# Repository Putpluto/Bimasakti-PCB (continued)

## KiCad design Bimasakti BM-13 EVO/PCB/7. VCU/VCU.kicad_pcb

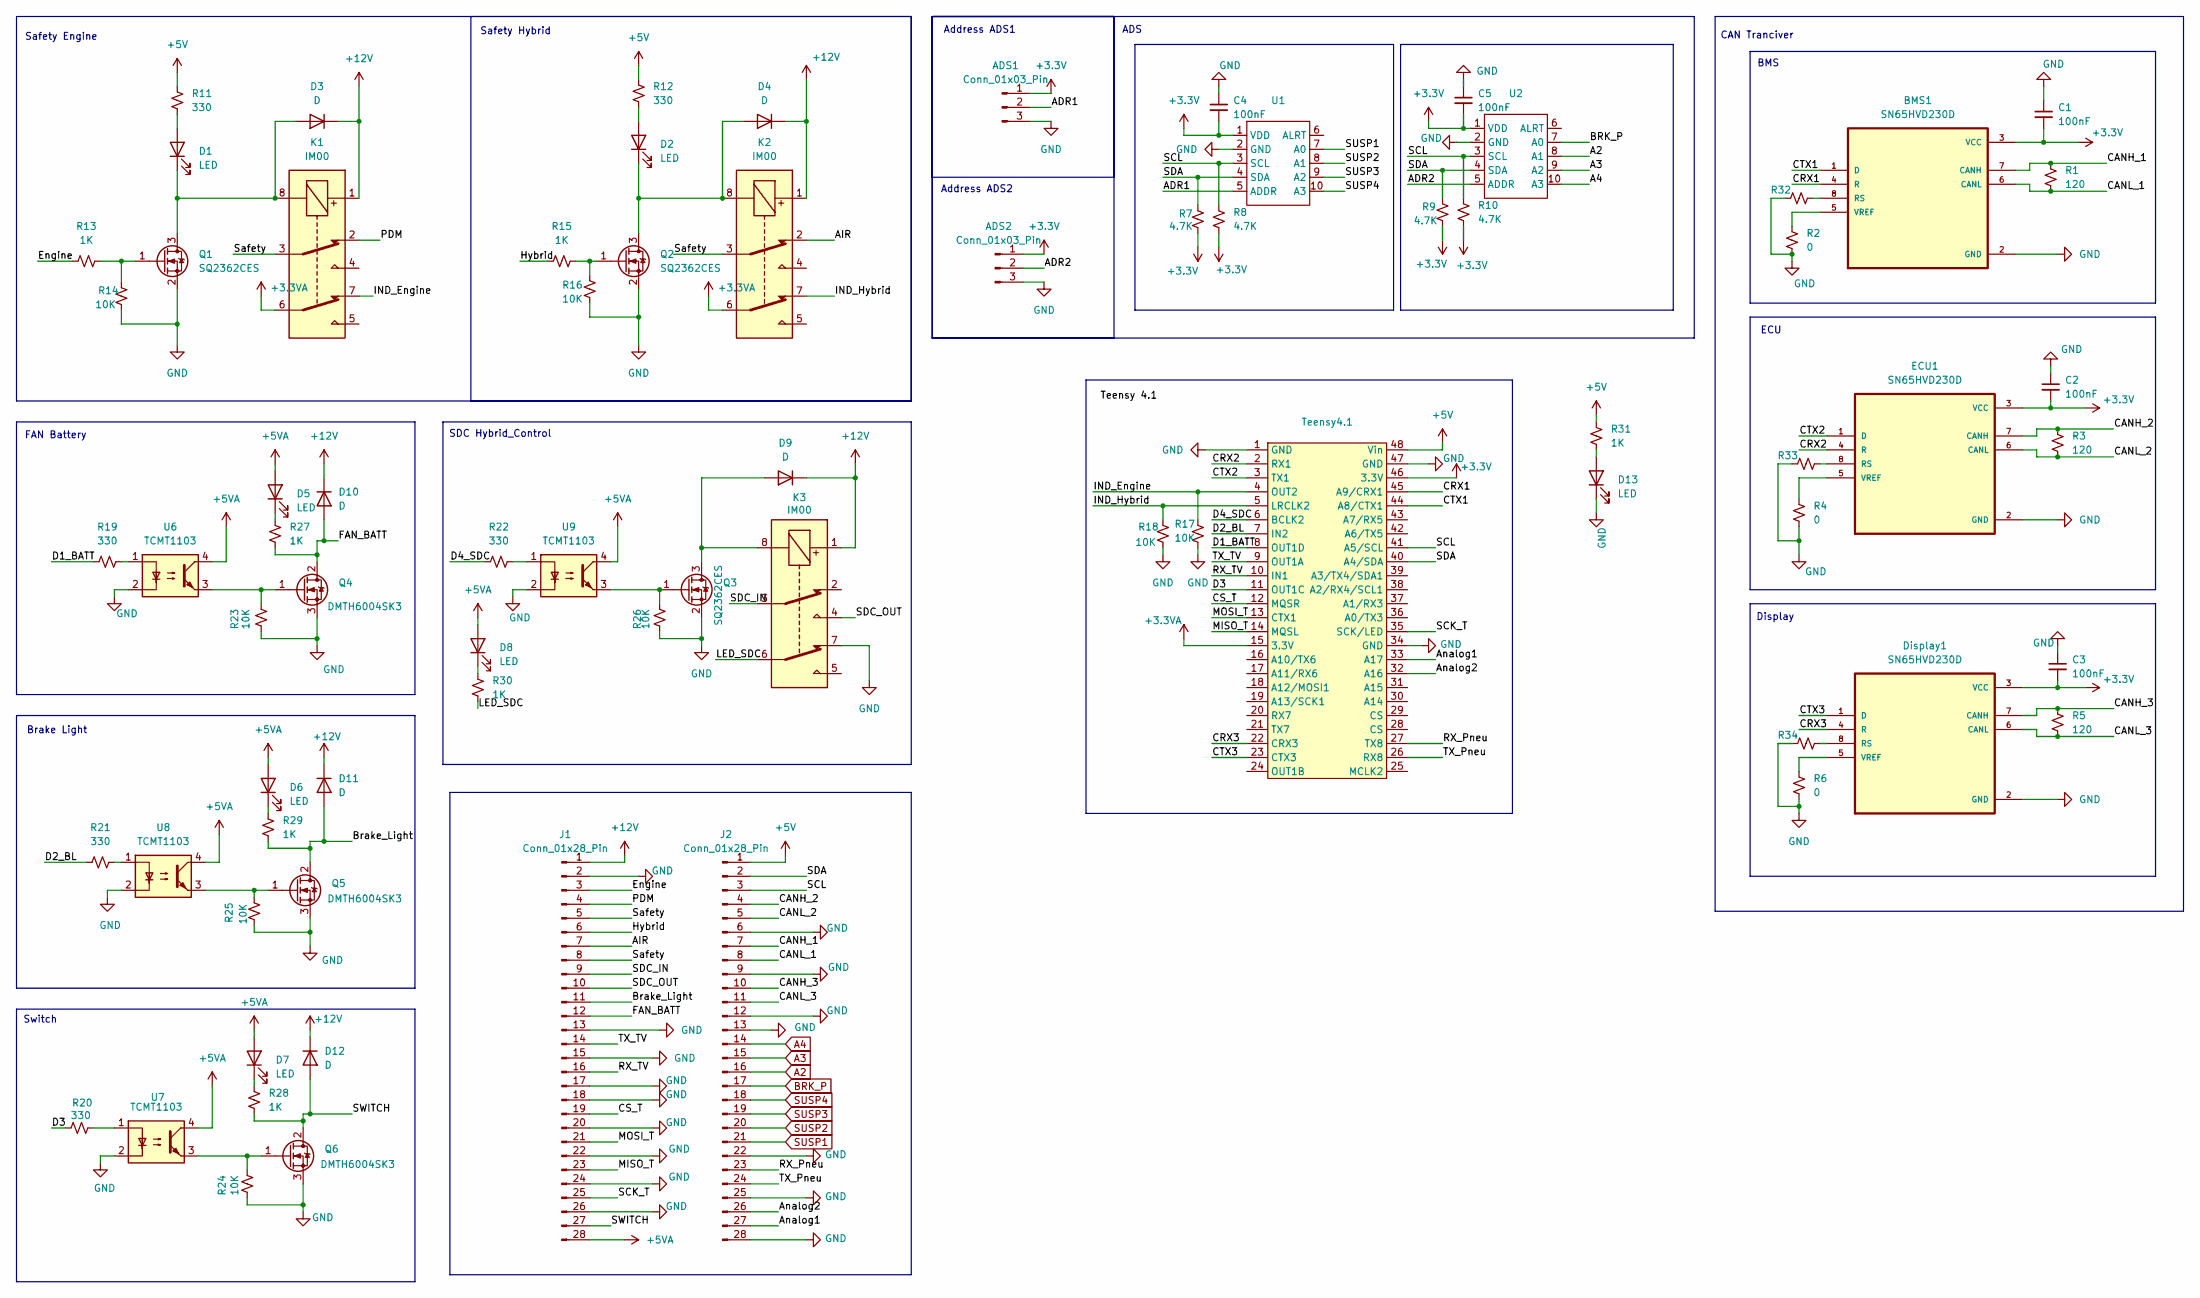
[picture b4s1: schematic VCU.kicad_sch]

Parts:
ADS1, ADS2: Conn_01x03_Pin; PinHeader_1x03_P2.54mm_Vertical
BMS1: SN65HVD230D; SOIC127P599X175-8N
C1, C2, C3, C4, C5: 100nF; C_0603_1608Metric_Pad1.08x0.95mm_HandSolder
D1, D2, D5, D6, D7, D8, D13: LED; LED_0603_1608Metric_Pad1.05x0.95mm_HandSolder
D3, D4, D9, D10, D11, D12: D; D_SOD-123
Display1: SN65HVD230D; SOIC127P599X175-8N
ECU1: SN65HVD230D; SOIC127P599X175-8N
J1, J2: Conn_01x28_Pin; PinHeader_1x28_P2.54mm_Vertical
K1, K2, K3: IM00; RELAY8-TH_NON-LATCH_1-COIL
Q1, Q2, Q3: SQ2362CES; SOT-23
Q4, Q5, Q6: DMTH6004SK3; TO-252-2
R1, R3, R5: 120; R_0603_1608Metric_Pad0.98x0.95mm_HandSolder
R2, R4, R6: 0; R_0603_1608Metric_Pad0.98x0.95mm_HandSolder
R7, R8, R9, R10: 4.7K; R_0603_1608Metric_Pad0.98x0.95mm_HandSolder
R11, R12, R19, R20, R21, R22: 330; R_0603_1608Metric_Pad0.98x0.95mm_HandSolder
R13, R15, R27, R28, R29, R30, R31: 1K; R_0603_1608Metric_Pad0.98x0.95mm_HandSolder
R14, R16, R17, R18, R23, R24, R25, R26: 10K; R_0603_1608Metric_Pad0.98x0.95mm_HandSolder
R32, R33, R34: R_Small_US; R_0603_1608Metric_Pad0.98x0.95mm_HandSolder
Teensy4.1: Teensy41
U1, U2: MSOP10
U6, U7, U8, U9: TCMT1103; SOP-4_4.4x2.6mm_P1.27mm

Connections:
+3.3V: ADS1.1, ADS2.1, BMS1.3 (VCC), C1.2, C2.2, C3.2, C4.2, C5.2, Display1.3 (VCC), ECU1.3 (VCC), R7.2, R8.2, R9.2, R10.2, Teensy4.1.46 (3.3V), U1.1 (VDD), U2.1 (VDD)
+3.3VA: K1.6, K2.6, Teensy4.1.15 (3.3V)
+5V: J2.1, R11.1, R12.1, R31.1, Teensy4.1.48 (Vin)
+5VA: D5.2 (A), D6.2 (A), D7.2 (A), D8.2 (A), J1.28, U6.4, U7.4, U8.4, U9.4
+12V: D3.1 (K), D4.1 (K), D9.1 (K), D10.1 (K), D11.1 (K), D12.1 (K), J1.1, K1.1, K2.1, K3.1
/ADR1: ADS1.2, U1.5 (ADDR)
/ADR2: ADS2.2, U2.5 (ADDR)
/AIR: J1.7, K2.2
/Analog1: J2.27, Teensy4.1.33 (A17)
/Analog2: J2.26, Teensy4.1.32 (A16)
/Brake_Light: D11.2 (A), J1.11, Q5.2 (D), R29.2
/CANH_1: BMS1.7 (CANH), J2.7, R1.1
/CANH_2: ECU1.7 (CANH), J2.4, R3.1
/CANH_3: Display1.7 (CANH), J2.10, R5.1
/CANL_1: BMS1.6 (CANL), J2.8, R1.2
/CANL_2: ECU1.6 (CANL), J2.5, R3.2
/CANL_3: Display1.6 (CANL), J2.11, R5.2
/CRX1: BMS1.4 (R), Teensy4.1.45 (A9/CRX1)
/CRX2: ECU1.4 (R), Teensy4.1.2 (RX1)
/CRX3: Display1.4 (R), Teensy4.1.22 (CRX3)
/CS_T: J1.19, Teensy4.1.12 (MQSR)
/CTX1: BMS1.1 (D), Teensy4.1.44 (A8/CTX1)
/CTX2: ECU1.1 (D), Teensy4.1.3 (TX1)
/CTX3: Display1.1 (D), Teensy4.1.23 (CTX3)
/D1_BATT: R19.1, Teensy4.1.8 (OUT1D)
/D2_BL: R21.1, Teensy4.1.7 (IN2)
/D3: R20.1, Teensy4.1.11 (OUT1C)
/D4_SDC: R22.1, Teensy4.1.6 (BCLK2)
/Engine: J1.3, R13.1
/FAN_BATT: D10.2 (A), J1.12, Q4.2 (D), R27.2
/Hybrid: J1.6, R15.1
/IND_Engine: K1.7, R17.1, Teensy4.1.4 (OUT2)
/IND_Hybrid: K2.7, R18.1, Teensy4.1.5 (LRCLK2)
/LED_SDC: K3.6, R30.2
/MISO_T: J1.23, Teensy4.1.14 (MQSL)
/MOSI_T: J1.21, Teensy4.1.13 (CTX1)
/PDM: J1.4, K1.2
/RX_Pneu: J2.23, Teensy4.1.27 (TX8)
/RX_TV: J1.16, Teensy4.1.10 (IN1)
/SCK_T: J1.25, Teensy4.1.35 (SCK/LED)
/SCL: J2.3, R8.1, R10.1, Teensy4.1.41 (A5/SCL), U1.3 (SCL), U2.3 (SCL)
/SDA: J2.2, R7.1, R9.1, Teensy4.1.40 (A4/SDA), U1.4 (SDA), U2.4 (SDA)
/SDC_IN: J1.9, K3.3
/SDC_OUT: J1.10, K3.4
/SWITCH: D12.2 (A), J1.27, Q6.2 (D), R28.2
/Safety: J1.5, J1.8, K1.3, K2.3
/TX_Pneu: J2.24, Teensy4.1.26 (RX8)
/TX_TV: J1.14, Teensy4.1.9 (OUT1A)
A2: J2.16, U2.8 (A1)
A3: J2.15, U2.9 (A2)
A4: J2.14, U2.10 (A3)
BRK_P: J2.17, U2.7 (A0)
GND: ADS1.3, ADS2.3, BMS1.2 (GND), C1.1, C2.1, C3.1, C4.1, C5.1, D13.1 (K), Display1.2 (GND), ECU1.2 (GND), J1.2, J1.13, J1.15, J1.17, J1.18, J1.20, J1.22, J1.24, J1.26, J2.6, J2.9, J2.12, J2.13, J2.22, J2.25, J2.28, K3.7, Q1.2 (S), Q2.2 (S), Q3.2 (S), Q4.3 (S), Q5.3 (S), Q6.3 (S), R2.2, R4.2, R6.2, R14.2, R16.2, R17.2, R18.2, R23.1, R24.1, R25.1, R26.1, R32.2, R33.2, R34.2, Teensy4.1.1 (GND), Teensy4.1.34 (GND), Teensy4.1.47 (GND), U1.2 (GND), U2.2 (GND), U6.2, U7.2, U8.2, U9.2
unnamed: BMS1.8 (RS), R32.1
unnamed: BMS1.5 (VREF), R2.1
unnamed: D1.2 (A), R11.2
unnamed: D1.1 (K), D3.2 (A), K1.8, Q1.3 (D)
unnamed: D2.2 (A), R12.2
unnamed: D2.1 (K), D4.2 (A), K2.8, Q2.3 (D)
unnamed: D5.1 (K), R27.1
unnamed: D6.1 (K), R29.1
unnamed: D7.1 (K), R28.1
unnamed: D8.1 (K), R30.1
unnamed: D9.2 (A), K3.8, Q3.3 (D)
unnamed: D13.2 (A), R31.2
unnamed: Display1.8 (RS), R34.1
unnamed: Display1.5 (VREF), R6.1
unnamed: ECU1.8 (RS), R33.1
unnamed: ECU1.5 (VREF), R4.1
unnamed: Q1.1 (G), R13.2, R14.1
unnamed: Q2.1 (G), R15.2, R16.1
unnamed: Q3.1 (G), R26.2, U9.3
unnamed: Q4.1 (G), R23.2, U6.3
unnamed: Q5.1 (G), R25.2, U8.3
unnamed: Q6.1 (G), R24.2, U7.3
unnamed: R19.2, U6.1
unnamed: R20.2, U7.1
unnamed: R21.2, U8.1
unnamed: R22.2, U9.1
SUSP1: J2.21, U1.7 (A0)
SUSP2: J2.20, U1.8 (A1)
SUSP3: J2.19, U1.9 (A2)
SUSP4: J2.18, U1.10 (A3)

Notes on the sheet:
Address ADS1
BMS
CAN Tranciver
FAN Battery
ADS
SDC Hybrid_Control
Switch
Display
ECU
Safety Engine
Safety Hybrid
Brake Light
Address ADS2

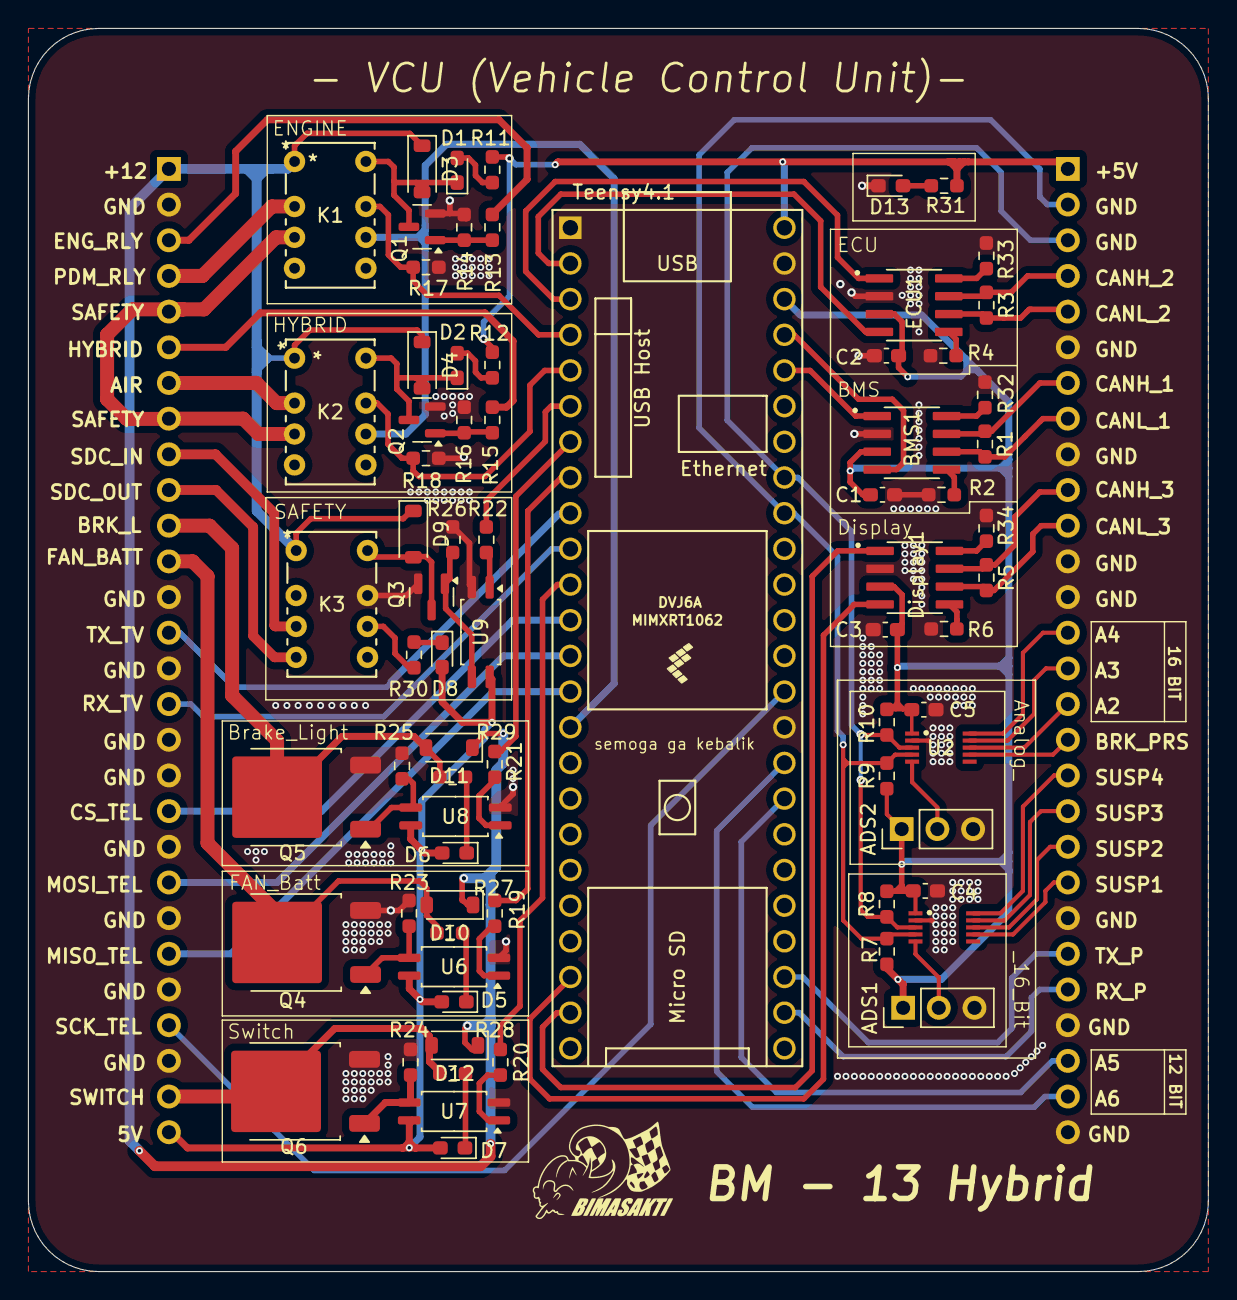
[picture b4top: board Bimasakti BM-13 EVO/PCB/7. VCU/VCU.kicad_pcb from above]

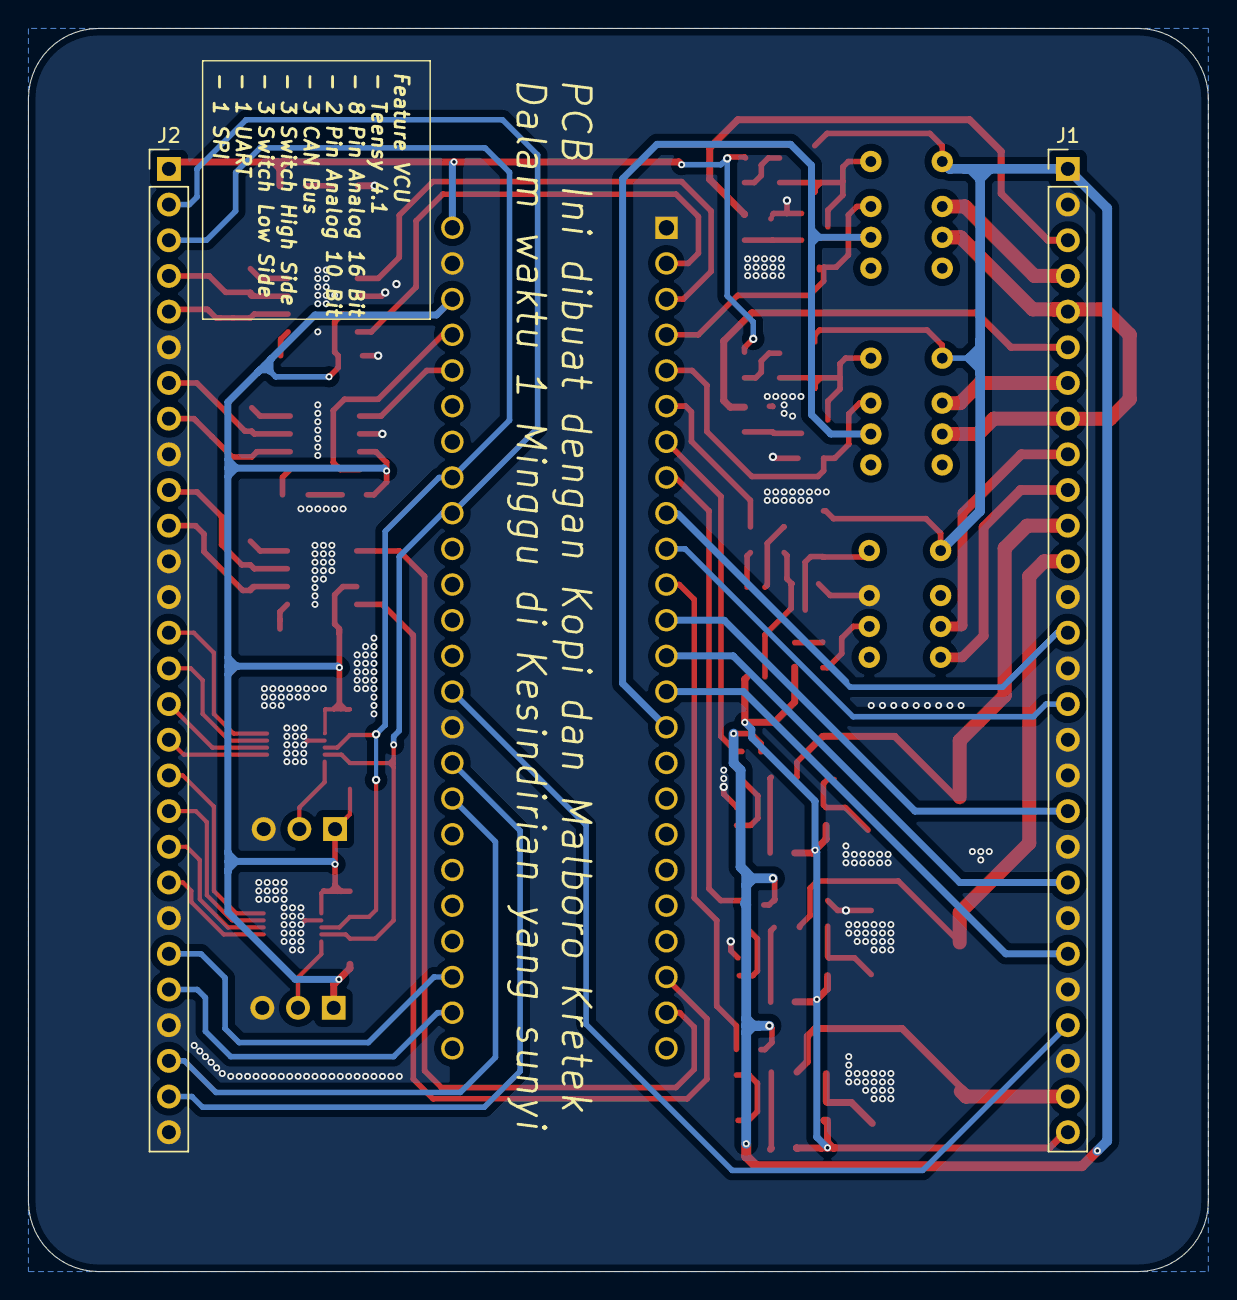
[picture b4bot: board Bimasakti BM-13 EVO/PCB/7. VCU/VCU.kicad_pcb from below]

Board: 2 copper layers, 84.0 x 88.5 mm, 75 parts (2 on the bottom side), 83 nets.

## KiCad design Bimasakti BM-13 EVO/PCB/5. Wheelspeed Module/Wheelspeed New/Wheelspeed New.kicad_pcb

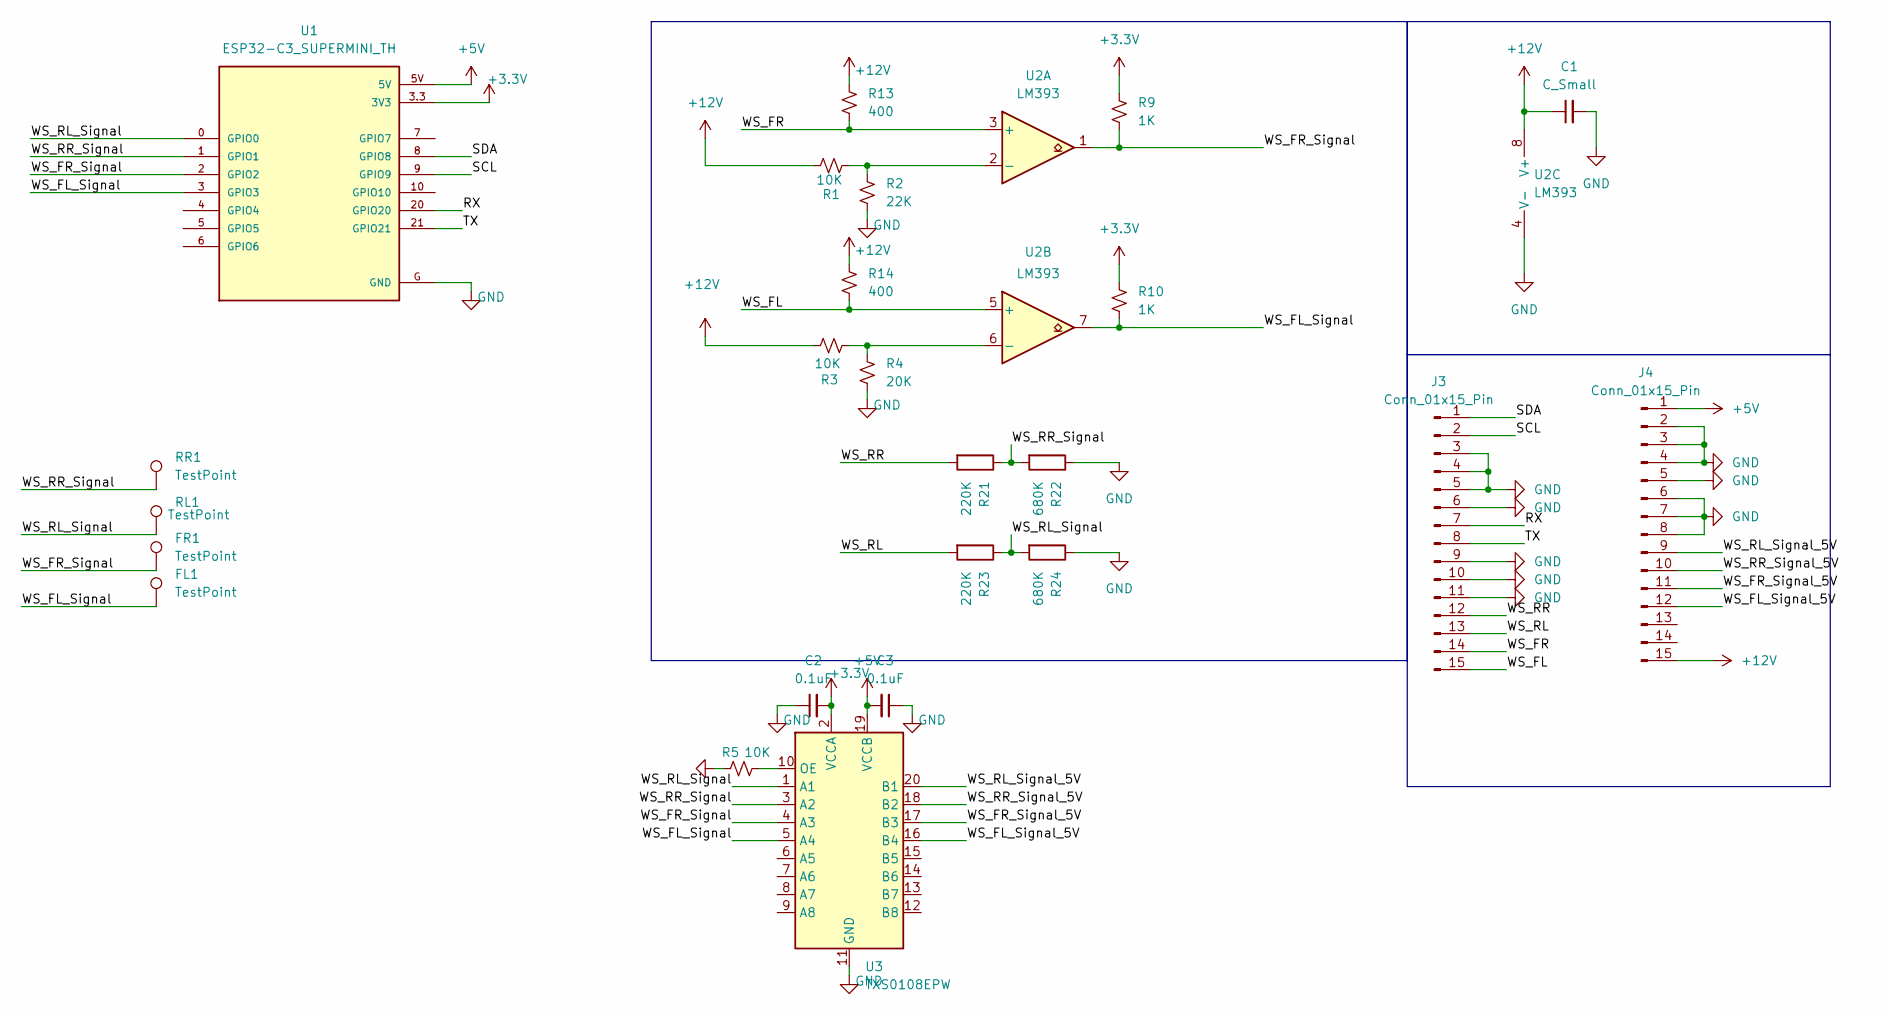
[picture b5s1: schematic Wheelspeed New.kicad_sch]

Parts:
C1: C_Small; C_0603_1608Metric_Pad1.08x0.95mm_HandSolder
C2, C3: 0.1uF; C_0603_1608Metric_Pad1.08x0.95mm_HandSolder
FL1: TestPoint; TestPoint_Bridge_Pitch2.54mm_Drill0.7mm
FR1: TestPoint; TestPoint_Bridge_Pitch2.54mm_Drill0.7mm
J3, J4: Conn_01x15_Pin; PinHeader_1x15_P2.54mm_Vertical
R1, R3, R5: 10K; R_0603_1608Metric_Pad0.98x0.95mm_HandSolder
R2: 22K; R_0603_1608Metric_Pad0.98x0.95mm_HandSolder
R4: 20K; R_0603_1608Metric_Pad0.98x0.95mm_HandSolder
R9, R10: 1K; R_0603_1608Metric_Pad0.98x0.95mm_HandSolder
R13, R14: 400; R_0603_1608Metric_Pad0.98x0.95mm_HandSolder
R21, R23: 220K; R_0603_1608Metric_Pad0.98x0.95mm_HandSolder
R22, R24: 680K; R_0603_1608Metric_Pad0.98x0.95mm_HandSolder
RL1: TestPoint; TestPoint_Bridge_Pitch2.54mm_Drill0.7mm
RR1: TestPoint; TestPoint_Bridge_Pitch2.54mm_Drill0.7mm
U1: ESP32-C3_SUPERMINI_TH; MODULE_ESP32-C3_SUPERMINI
U2: LM393; SO8_STM
U3: TXS0108EPW; TSSOP-20_4.4x6.5mm_P0.65mm

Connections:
+3.3V: C2.2, R9.1, R10.1, U1.3.3 (3V3), U3.2 (VCCA)
+5V: C3.2, J4.1, U1.5V, U3.19 (VCCB)
+12V: C1.1, J4.15, R1.1, R3.1, R13.1, R14.1, U2.8 (V+)
/RX: J3.7, U1.20 (GPIO20)
/SCL: J3.2, U1.9 (GPIO9)
/SDA: J3.1, U1.8 (GPIO8)
/TX: J3.8, U1.21 (GPIO21)
/WS_FL: J3.15, R14.2, U2.5 (+)
/WS_FL_Signal: FL1.1, R10.2, U1.3 (GPIO3), U2.7, U3.5 (A4)
/WS_FL_Signal_5V: J4.12, U3.16 (B4)
/WS_FR: J3.14, R13.2, U2.3 (+)
/WS_FR_Signal: FR1.1, R9.2, U1.2 (GPIO2), U2.1, U3.4 (A3)
/WS_FR_Signal_5V: J4.11, U3.17 (B3)
/WS_RL: J3.13, R23.2
/WS_RL_Signal: R23.1, R24.2, RL1.1, U1.0 (GPIO0), U3.1 (A1)
/WS_RL_Signal_5V: J4.9, U3.20 (B1)
/WS_RR: J3.12, R21.2
/WS_RR_Signal: R21.1, R22.2, RR1.1, U1.1 (GPIO1), U3.3 (A2)
/WS_RR_Signal_5V: J4.10, U3.18 (B2)
GND: C1.2, C2.1, C3.1, J3.3, J3.4, J3.5, J3.6, J3.9, J3.10, J3.11, J4.2, J4.3, J4.4, J4.5, J4.6, J4.7, J4.8, R2.2, R4.2, R5.1, R22.1, R24.1, U1.G (GND), U2.4 (V-), U3.11 (GND)
unnamed: R1.2, R2.1, U2.2 (-)
unnamed: R3.2, R4.1, U2.6 (-)
unnamed: R5.2, U3.10 (OE)

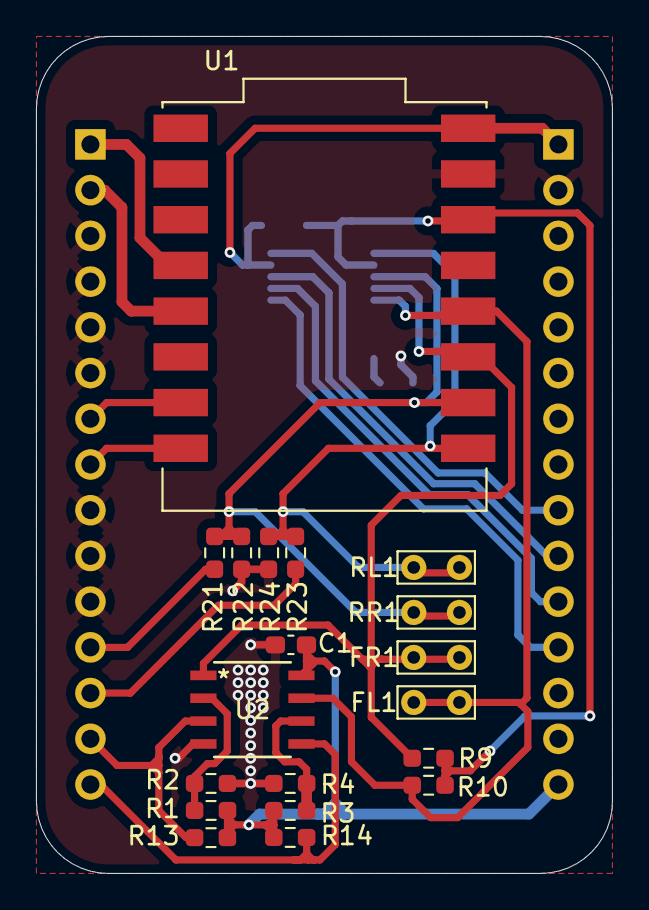
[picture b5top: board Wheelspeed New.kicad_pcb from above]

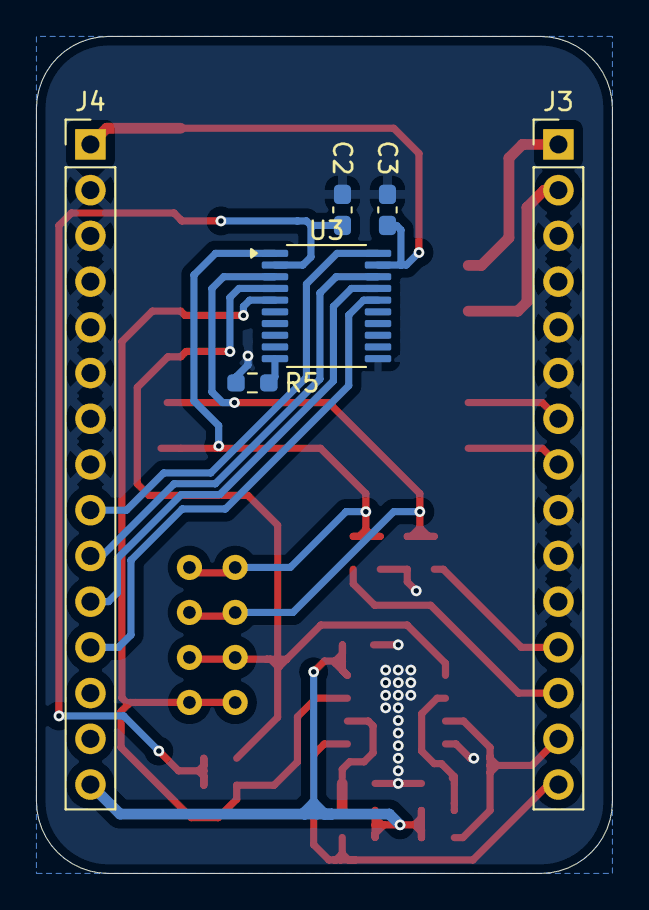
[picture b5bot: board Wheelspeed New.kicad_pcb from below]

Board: 2 copper layers, 32.0 x 46.5 mm, 25 parts (6 on the bottom side), 23 nets.

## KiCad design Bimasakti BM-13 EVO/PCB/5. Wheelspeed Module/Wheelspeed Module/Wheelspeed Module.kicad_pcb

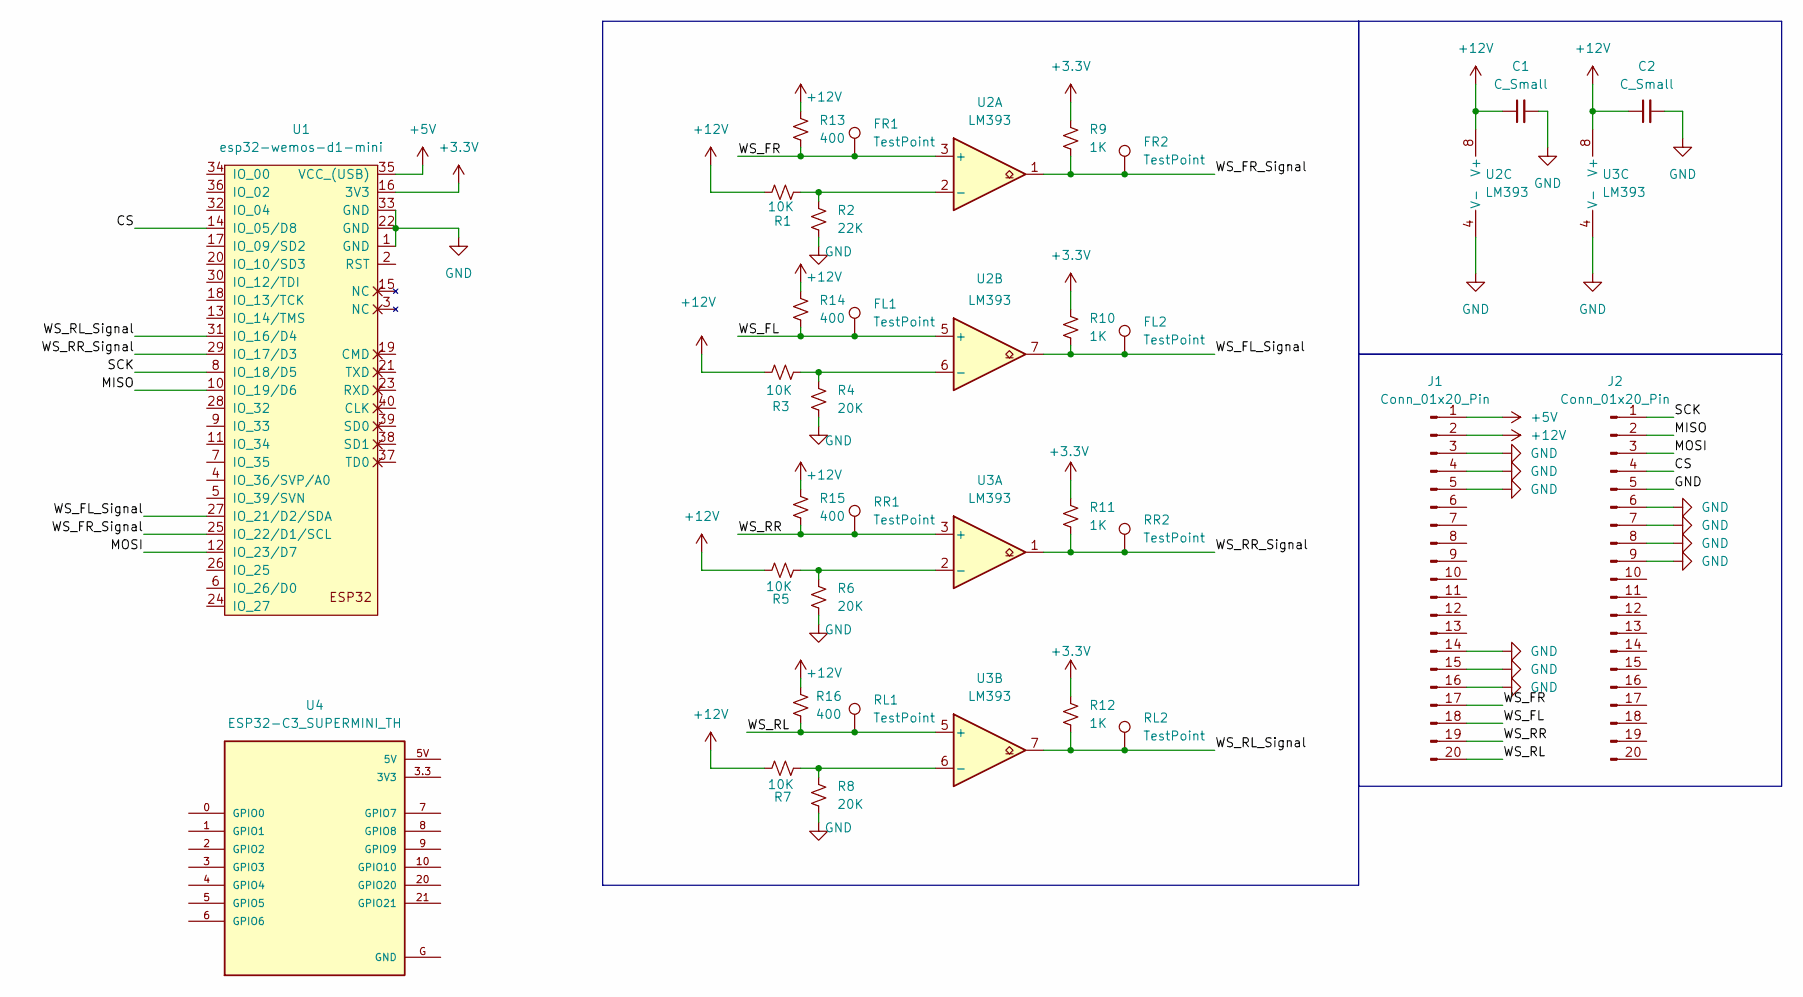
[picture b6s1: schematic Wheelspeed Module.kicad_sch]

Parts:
C1, C2: C_Small; C_0603_1608Metric_Pad1.08x0.95mm_HandSolder
FL1, FL2: TestPoint; TestPoint_Bridge_Pitch2.54mm_Drill0.7mm
FR1, FR2: TestPoint; TestPoint_Bridge_Pitch2.54mm_Drill0.7mm
J1, J2: Conn_01x20_Pin; PinHeader_1x20_P2.54mm_Vertical
R1, R3, R5, R7: 10K; R_0603_1608Metric_Pad0.98x0.95mm_HandSolder
R2: 22K; R_0603_1608Metric_Pad0.98x0.95mm_HandSolder
R4, R6, R8: 20K; R_0603_1608Metric_Pad0.98x0.95mm_HandSolder
R9, R10, R11, R12: 1K; R_0603_1608Metric_Pad0.98x0.95mm_HandSolder
R13, R14, R15, R16: 400; R_0603_1608Metric_Pad0.98x0.95mm_HandSolder
RL1, RL2: TestPoint; TestPoint_Bridge_Pitch2.54mm_Drill0.7mm
RR1, RR2: TestPoint; TestPoint_Bridge_Pitch2.54mm_Drill0.7mm
U1: esp32-wemos-d1-mini
U2, U3: LM393; SO8_STM
U4: ESP32-C3_SUPERMINI_TH; MODULE_ESP32-C3_SUPERMINI

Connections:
+3.3V: R9.1, R10.1, R11.1, R12.1, U1.16 (3V3)
+5V: J1.1, U1.35 (VCC_(USB))
+12V: C1.1, C2.1, J1.2, R1.1, R3.1, R5.1, R7.1, R13.1, R14.1, R15.1, R16.1, U2.8 (V+), U3.8 (V+)
/CS: J2.4, U1.14 (IO_05/D8)
/MISO: J2.2, U1.10 (IO_19/D6)
/MOSI: J2.3, U1.12 (IO_23/D7)
/SCK: J2.1, U1.8 (IO_18/D5)
/WS_FL: FL1.1, J1.18, R14.2, U2.5 (+)
/WS_FL_Signal: FL2.1, R10.2, U1.27 (IO_21/D2/SDA), U2.7
/WS_FR: FR1.1, J1.17, R13.2, U2.3 (+)
/WS_FR_Signal: FR2.1, R9.2, U1.25 (IO_22/D1/SCL), U2.1
/WS_RL: J1.20, R16.2, RL1.1, U3.5 (+)
/WS_RL_Signal: R12.2, RL2.1, U1.31 (IO_16/D4), U3.7
/WS_RR: J1.19, R15.2, RR1.1, U3.3 (+)
/WS_RR_Signal: R11.2, RR2.1, U1.29 (IO_17/D3), U3.1
GND: C1.2, C2.2, J1.3, J1.4, J1.5, J1.14, J1.15, J1.16, J2.5, J2.6, J2.7, J2.8, J2.9, R2.2, R4.2, R6.2, R8.2, U1.1 (GND), U1.22 (GND), U1.33 (GND), U2.4 (V-), U3.4 (V-)
unnamed: R1.2, R2.1, U2.2 (-)
unnamed: R3.2, R4.1, U2.6 (-)
unnamed: R5.2, R6.1, U3.2 (-)
unnamed: R7.2, R8.1, U3.6 (-)

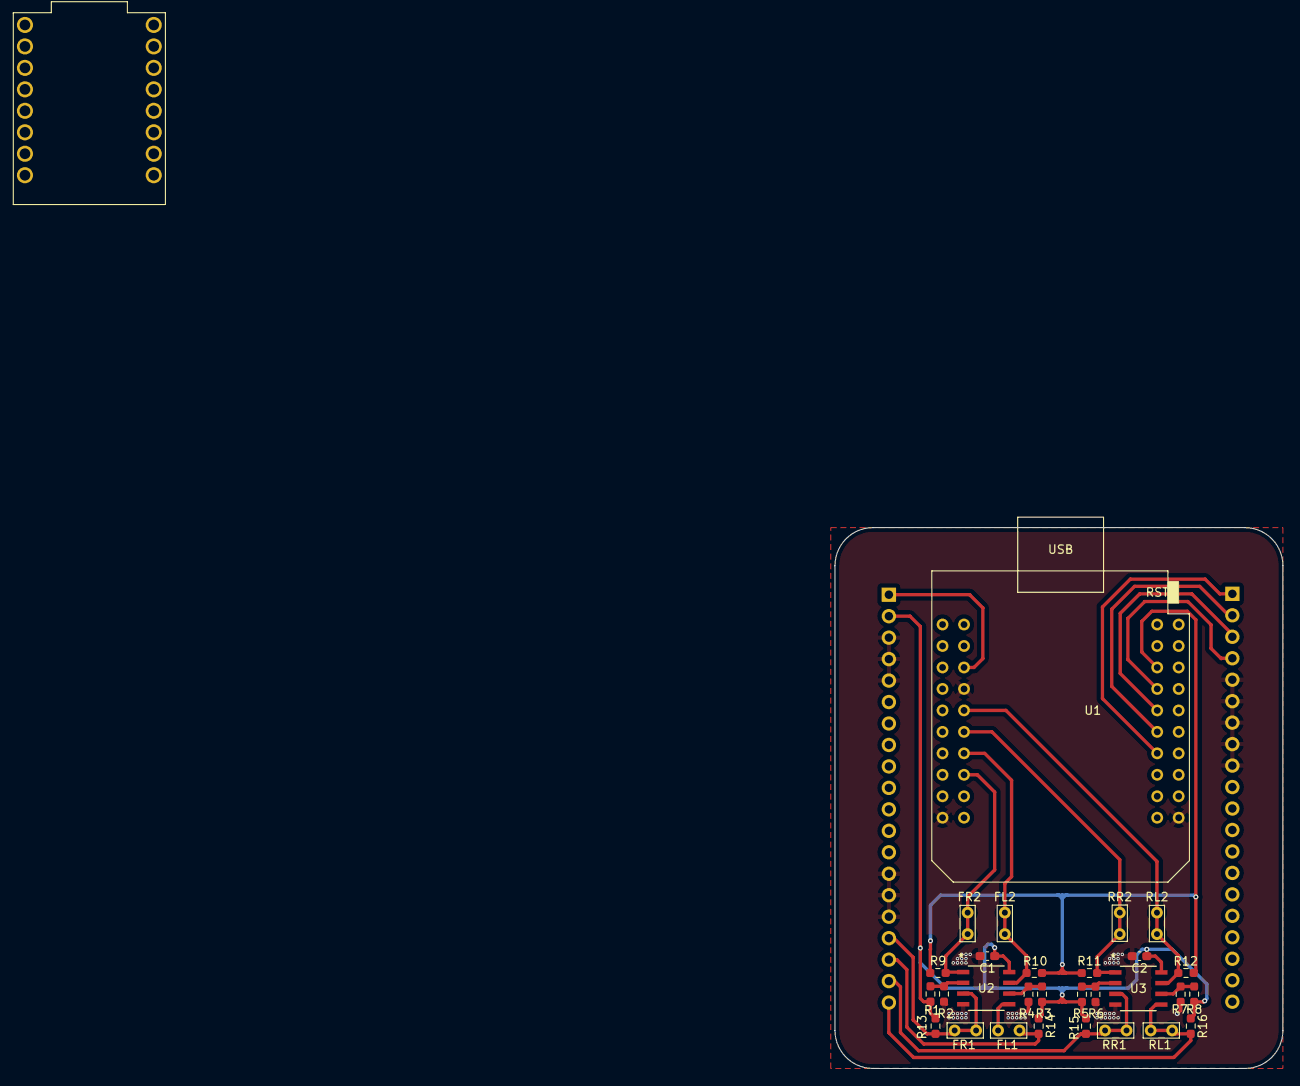
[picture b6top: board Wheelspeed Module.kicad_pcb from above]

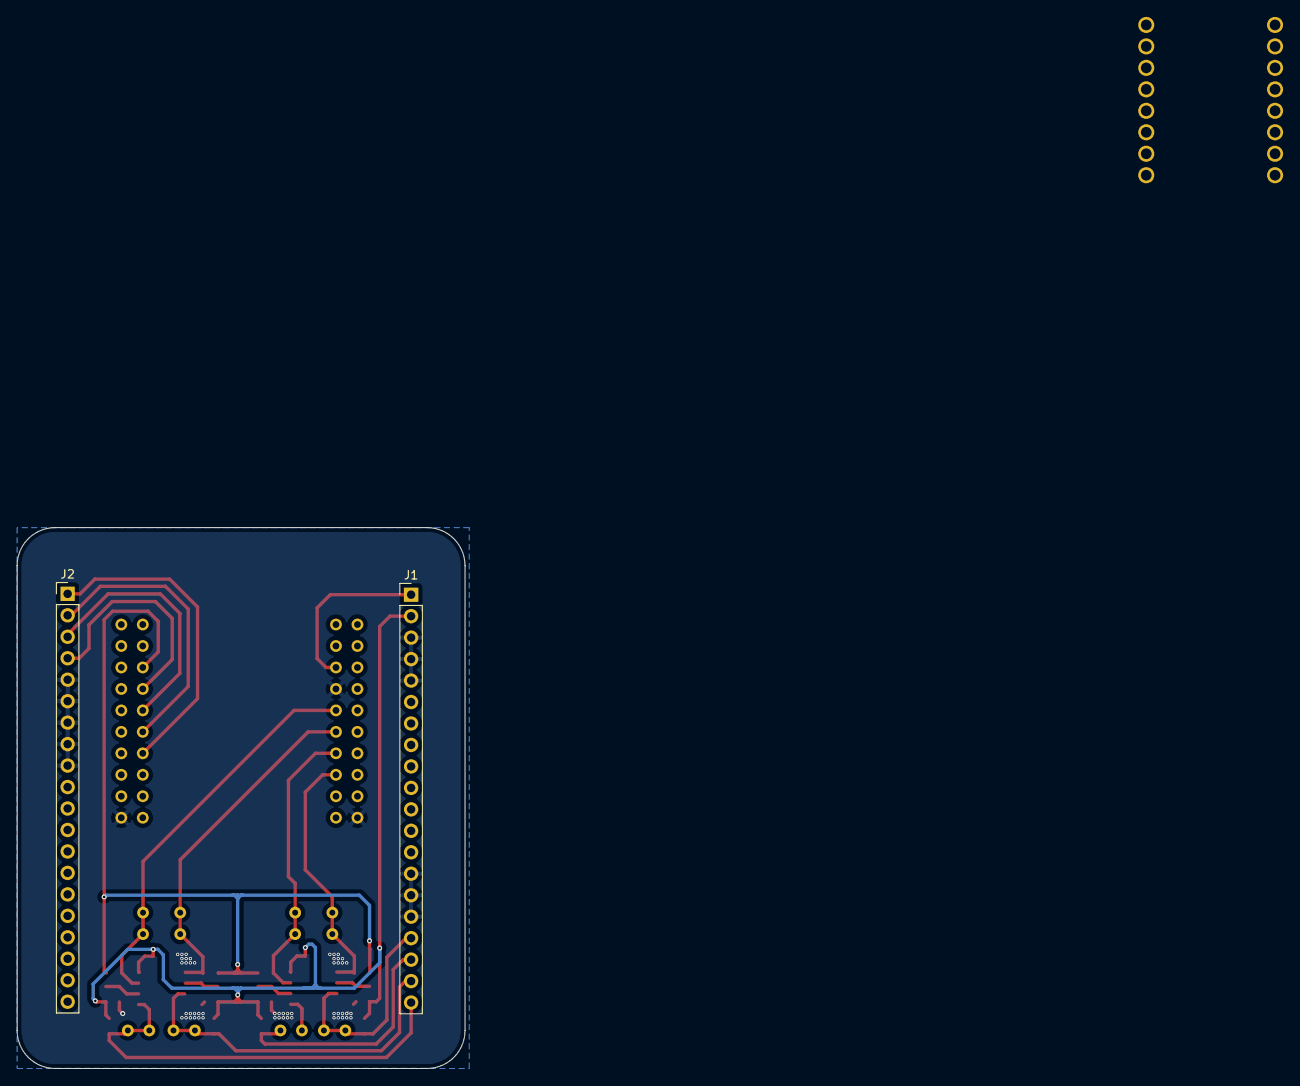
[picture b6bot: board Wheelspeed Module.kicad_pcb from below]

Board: 2 copper layers, 53.0 x 64.0 mm, 32 parts (2 on the bottom side), 20 nets.

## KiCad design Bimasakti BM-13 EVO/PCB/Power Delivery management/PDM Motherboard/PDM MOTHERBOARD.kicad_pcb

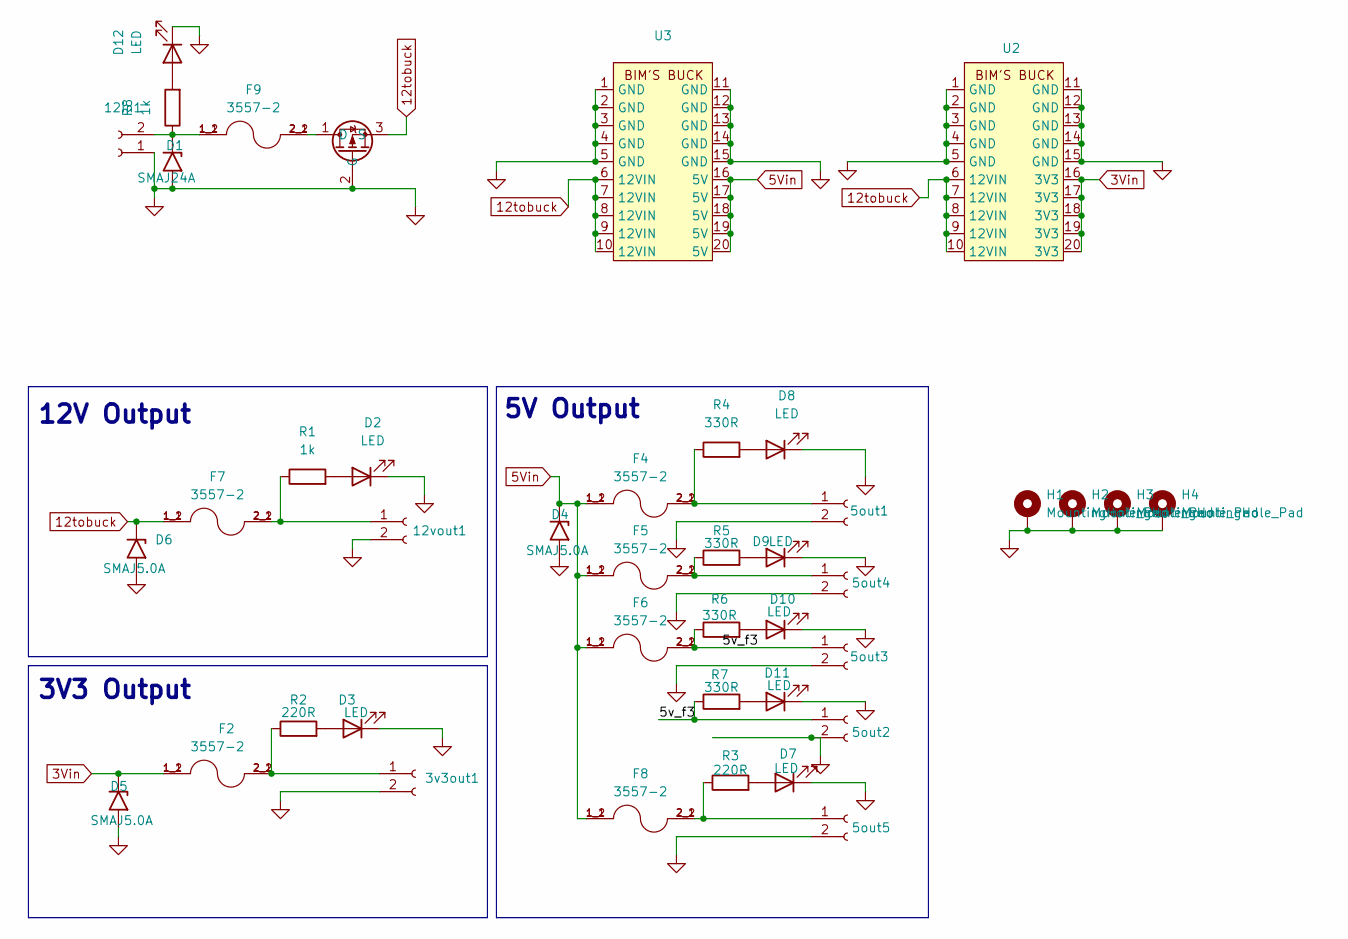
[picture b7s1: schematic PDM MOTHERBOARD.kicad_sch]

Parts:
3v3out1, 5out1, 5out3, 5out4, 5out5, 12vout1: JST_EH_B2B-EH-A_1x02_P2.50mm_Vertical
5out2: Molex_Nano-Fit_105309-xx02_1x02_P2.50mm_Vertical
12in1: TerminalBlock_Phoenix_MKDS-1,5-2_1x02_P5.00mm_Horizontal
D1: SMAJ24A; D_SMA
D2, D3, D7, D8, D9, D10, D11, D12: LED; LED_0805_2012Metric_Pad1.15x1.40mm_HandSolder
D4, D5, D6: SMAJ5.0A; D_SMA
F2, F4, F5, F6, F7, F8, F9: 3557-2; 0_FUSE_3557-2; PARTREV D
H1, H2, H3, H4: MountingHole_Pad; MountingHole_3.2mm_M3_ISO7380_Pad_TopBottom
R1, R8: 1k; R_0805_2012Metric_Pad1.20x1.40mm_HandSolder
R2, R3: 220R; R_0805_2012Metric_Pad1.20x1.40mm_HandSolder
R4, R5, R6, R7: 330R; R_0805_2012Metric_Pad1.20x1.40mm_HandSolder
U1: SOIC-8 (AOD)
U2, U3: BIMS_BUCK

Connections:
3Vin: D5.1 (A1), F2.1_1, F2.1_2, U2.16 (3V3), U2.17 (3V3), U2.18 (3V3), U2.19 (3V3), U2.20 (3V3)
5Vin: D4.1 (A1), F4.1_1, F4.1_2, F5.1_1, F5.1_2, F6.1_1, F6.1_2, F8.1_1, F8.1_2, U3.16 (5V), U3.17 (5V), U3.18 (5V), U3.19 (5V), U3.20 (5V)
12tobuck: D6.1 (A1), F7.1_1, F7.1_2, U1.3 (S), U2.6 (12VIN), U2.7 (12VIN), U2.8 (12VIN), U2.9 (12VIN), U2.10 (12VIN), U3.6 (12VIN), U3.7 (12VIN), U3.8 (12VIN), U3.9 (12VIN), U3.10 (12VIN)
/5v_f3: 5out2.1, 5out3.1, F6.2_1, F6.2_2, R6.1, R7.1
GND: 3v3out1.2, 5out1.2, 5out2.2, 5out3.2, 5out4.2, 5out5.2, 12in1.1, 12vout1.2, D1.2 (A2), D2.1 (K), D3.1 (K), D4.2 (A2), D5.2 (A2), D6.2 (A2), D7.1 (K), D8.1 (K), D9.1 (K), D10.1 (K), D11.1 (K), D12.1 (K), H1.1, H2.1, H3.1, H4.1, U1.2 (G), U2.1 (GND), U2.2 (GND), U2.3 (GND), U2.4 (GND), U2.5 (GND), U2.11 (GND), U2.12 (GND), U2.13 (GND), U2.14 (GND), U2.15 (GND), U3.1 (GND), U3.2 (GND), U3.3 (GND), U3.4 (GND), U3.5 (GND), U3.11 (GND), U3.12 (GND), U3.13 (GND), U3.14 (GND), U3.15 (GND)
unnamed: 3v3out1.1, F2.2_1, F2.2_2, R2.1
unnamed: 5out1.1, F4.2_1, F4.2_2, R4.1
unnamed: 5out4.1, F5.2_1, F5.2_2, R5.1
unnamed: 5out5.1, F8.2_1, F8.2_2, R3.1
unnamed: 12in1.2, D1.1 (A1), F9.1_1, F9.1_2, R8.1
unnamed: 12vout1.1, F7.2_1, F7.2_2, R1.1
unnamed: D2.2 (A), R1.2
unnamed: D3.2 (A), R2.2
unnamed: D7.2 (A), R3.2
unnamed: D8.2 (A), R4.2
unnamed: D9.2 (A), R5.2
unnamed: D10.2 (A), R6.2
unnamed: D11.2 (A), R7.2
unnamed: D12.2 (A), R8.2
unnamed: F9.2_1, F9.2_2, U1.1 (D)

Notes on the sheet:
5V Output
3V3 Output
12V Output
